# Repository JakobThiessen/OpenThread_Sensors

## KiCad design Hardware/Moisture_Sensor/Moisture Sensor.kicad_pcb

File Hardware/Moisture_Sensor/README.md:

# Moisture Sensor (OpenThread)  

> Kapazitiver Bodenfeuchtesensor mit ESP32-H2 und Matter over Thread  
> **Version 1.0 — April 2026**

## Fehler

Fehler im Schlatplan!!!
R7, Q1 und Q2 nicht bestücken.
Verbindung von Q1/pin1 zu Q2/Pin2 wie
eingezeichnet herstellen und mit GPIO
ein und ausschalten.

## Übersicht

Batteriebetriebener kapazitiver Bodenfeuchtesensor für den Einsatz im Smart Home. Die Kommunikation erfolgt drahtlos über **Matter over Thread** mittels eines **ESP32-H2 Supermini** Moduls.

Das Sensordesign misst die Bodenfeuchte kapazitiv über eine interdigitale Elektrodenstruktur auf der PCB-Sonde und nutzt einen **NE555** Timer zur Frequenzerzeugung. Die gemessene Frequenz wird vom ESP32-H2 ausgewertet und über das Thread-Netzwerk übermittelt.

## PCB

| Oberseite | Unterseite |
|-----------|------------|
|  |  |

### Abmessungen

| Parameter | Wert |
|-----------|------|
| Gesamtlänge (inkl. Sonde) | ca. 90 mm |
| Breite Elektronikteil | ca. 28,4 mm |
| Breite Sonde | ca. 14,2 mm |

## Hauptkomponenten

| Bauteil | Beschreibung |
|---------|-------------|
| **ESP32-H2 Supermini** | Mikrocontroller mit IEEE 802.15.4 (Thread) |
| **NE555D** | Timer-IC für kapazitive Frequenzmessung |
| **BSS84** | P-Kanal MOSFET (Stromversorgungsschaltung) |
| **BSS123** | N-Kanal MOSFET (Sensor-Enable-Schaltung) |
| **BAS19** | Schaltdiode |
| **3,7 V LiPo** | Lithium-Polymer-Akku (auf der Rückseite montiert) |

## Signale

| Signal | Funktion |
|--------|----------|
| `SensorEN` | Aktiviert die Sensorschaltung (Stromsparen) |
| `SensorOut` | Frequenzausgang des NE555 → ESP32-H2 |
| `Ubat_adc` | Batteriespannungsmessung über ADC |
| `IO4`, `IO5` | Weitere GPIOs des ESP32-H2 |

## Funktionsprinzip

1. Der ESP32-H2 aktiviert die Sensorschaltung über `SensorEN` (MOSFET-Schaltstufe: Q1 BSS123 → Q2 BSS84).
2. Der NE555 erzeugt ein Rechtecksignal, dessen Frequenz von der Kapazität der Sonde abhängt.
3. Die Sonde nutzt interdigitale Kupferflächen — eine höhere Bodenfeuchte erhöht die Kapazität und senkt die Frequenz.
4. Der ESP32-H2 misst die Frequenz am `SensorOut`-Pin und berechnet den Feuchtigkeitswert.
5. Nach der Messung wird die Sensorschaltung abgeschaltet, um Strom zu sparen.
6. Die Batteriespannung wird über `Ubat_adc` überwacht (Spannungsteiler R1/R6: 2MΩ/4,7MΩ → ca. 0,55 µA Ruhestrom).
7. Die Messwerte werden per **Matter over Thread** an den Thread Border Router gesendet.

## Schaltungsanalyse — NE555 Astable

### Timing-Beschaltung

Der NE555 ist als **Astable-Multivibrator** konfiguriert:

| Parameter | Bauteil | Wert |
|-----------|---------|------|
| Ra (VCC → Discharge) | R2 | 330 kΩ |
| Rb (Discharge → Threshold/Trigger) | R3 | 1,6 kΩ |
| C (Timing-Kondensator) | C3 | 470 pF |
| C_probe (Sonden-Kapazität) | PCB-Elektroden | variabel |
| CV-Bypass (Pin 5) | C6 | 10 nF |
| Abblock-Kondensator | C4 | 100 nF |

### Frequenzformel (NE555 Astable)

$$f = \frac{1{,}44}{(R_A + 2 \cdot R_B) \cdot C_{total}}$$

Mit $R_A = 330\,\text{k}\Omega$, $R_B = 1{,}6\,\text{k}\Omega$:

$$R_A + 2 \cdot R_B = 333{,}2\,\text{k}\Omega$$

Die Gesamtkapazität setzt sich zusammen aus dem Festkondensator C3 und der variablen Sondenkapazität:

$$C_{total} = C_3 + C_{probe} = 470\,\text{pF} + C_{probe}$$

### Berechnete Frequenzen

| Zustand | C_probe (geschätzt) | C_total | Frequenz |
|---------|---------------------|---------|----------|
| Nur C3 (kein Boden) | 0 pF | 470 pF | **9,19 kHz** |
| Luft / trockene Sonde | ~10 pF | 480 pF | **9,00 kHz** |
| Trockener Boden | ~50 pF | 520 pF | **8,31 kHz** |
| Mäßig feucht | ~150 pF | 620 pF | **6,97 kHz** |
| Nasser Boden | ~300 pF | 770 pF | **5,61 kHz** |
| Gesättigt / Wasser | ~500 pF | 970 pF | **4,46 kHz** |

**Erwarteter Frequenzbereich: ca. 4,5 kHz – 9,2 kHz**

### Duty Cycle

$$D = \frac{R_A + R_B}{R_A + 2 \cdot R_B} = \frac{331{,}6\,\text{k}}{333{,}2\,\text{k}} \approx 99{,}5\,\%$$

Das Signal ist stark asymmetrisch (sehr kurze Low-Pulse). Der ESP32-H2 sollte die **Periodendauer** oder **Frequenz** messen (z. B. per Timer-Capture), nicht das Tastverhältnis.

### Bewertung (KI) — Kann das Design funktionieren?

**Grundsätzlich: Ja**, mit folgenden Anmerkungen:

| Aspekt | Bewertung |
|--------|-----------|
| Frequenzbereich 4,5–9,2 kHz | Sehr gut messbar mit ESP32-H2 Timer/Counter |
| Auflösung | Bei 12-bit Timer-Capture ausreichende Auflösung über den gesamten Bereich |
| Power-Gating (BSS84/BSS123) | Sinnvolles Design für Batteriebetrieb |
| Batterie-Monitoring (2M/4,7M Teiler) | Sehr stromsparend (~0,55 µA), gutes Design |
| Interdigitale PCB-Sonde | Bewährtes Prinzip für kapazitive Feuchtemessung |

**Wichtiger Hinweis — Versorgungsspannung:**

> ⚠️ Der klassische **NE555** (bipolar) ist für **min. 4,5 V** spezifiziert. Bei **3,3 V** Betriebsspannung kann er unzuverlässig arbeiten oder gar nicht anlaufen. Es wird empfohlen, eine **CMOS-555-Variante** zu verwenden (z. B. **LMC555**, **TLC555**, **ICM7555**), die ab **1,5 V** arbeitet und zudem weniger Strom verbraucht. Der Footprint (SOIC-8) ist kompatibel.

### Tipps zur Kalibrierung

- Den Sensor in **trockener Luft** und in **Wasser** messen → Frequenz-Endwerte bestimmen.
- Einen linearen oder polynomialen Zusammenhang zwischen Frequenz und Feuchte kalibrieren.
- Die Sondenkapazität hängt stark von Bodenart und Temperatur ab — eine Vor-Ort-Kalibrierung ist sinnvoll.

## Projektdateien

| Datei | Inhalt |
|-------|--------|
| `Moisture Sensor.kicad_sch` | Schaltplan |
| `Moisture Sensor.kicad_pcb` | PCB-Layout |
| `Moisture Sensor.kicad_pro` | KiCad-Projektdatei |
| `Moisture Sensor.step` | 3D-Modell der Platine |
| `Moisture Sensor.pdf` | Schaltplan als PDF |
| `lib/` | Bauteilbibliotheken (Symbole, Footprints, 3D-Modelle) |

## Voraussetzungen

- [KiCad 9.0](https://www.kicad.org/) oder neuer
- Thread Border Router (z. B. Apple HomePod, Google Nest Hub) für die Matter-Integration

## Lizenz

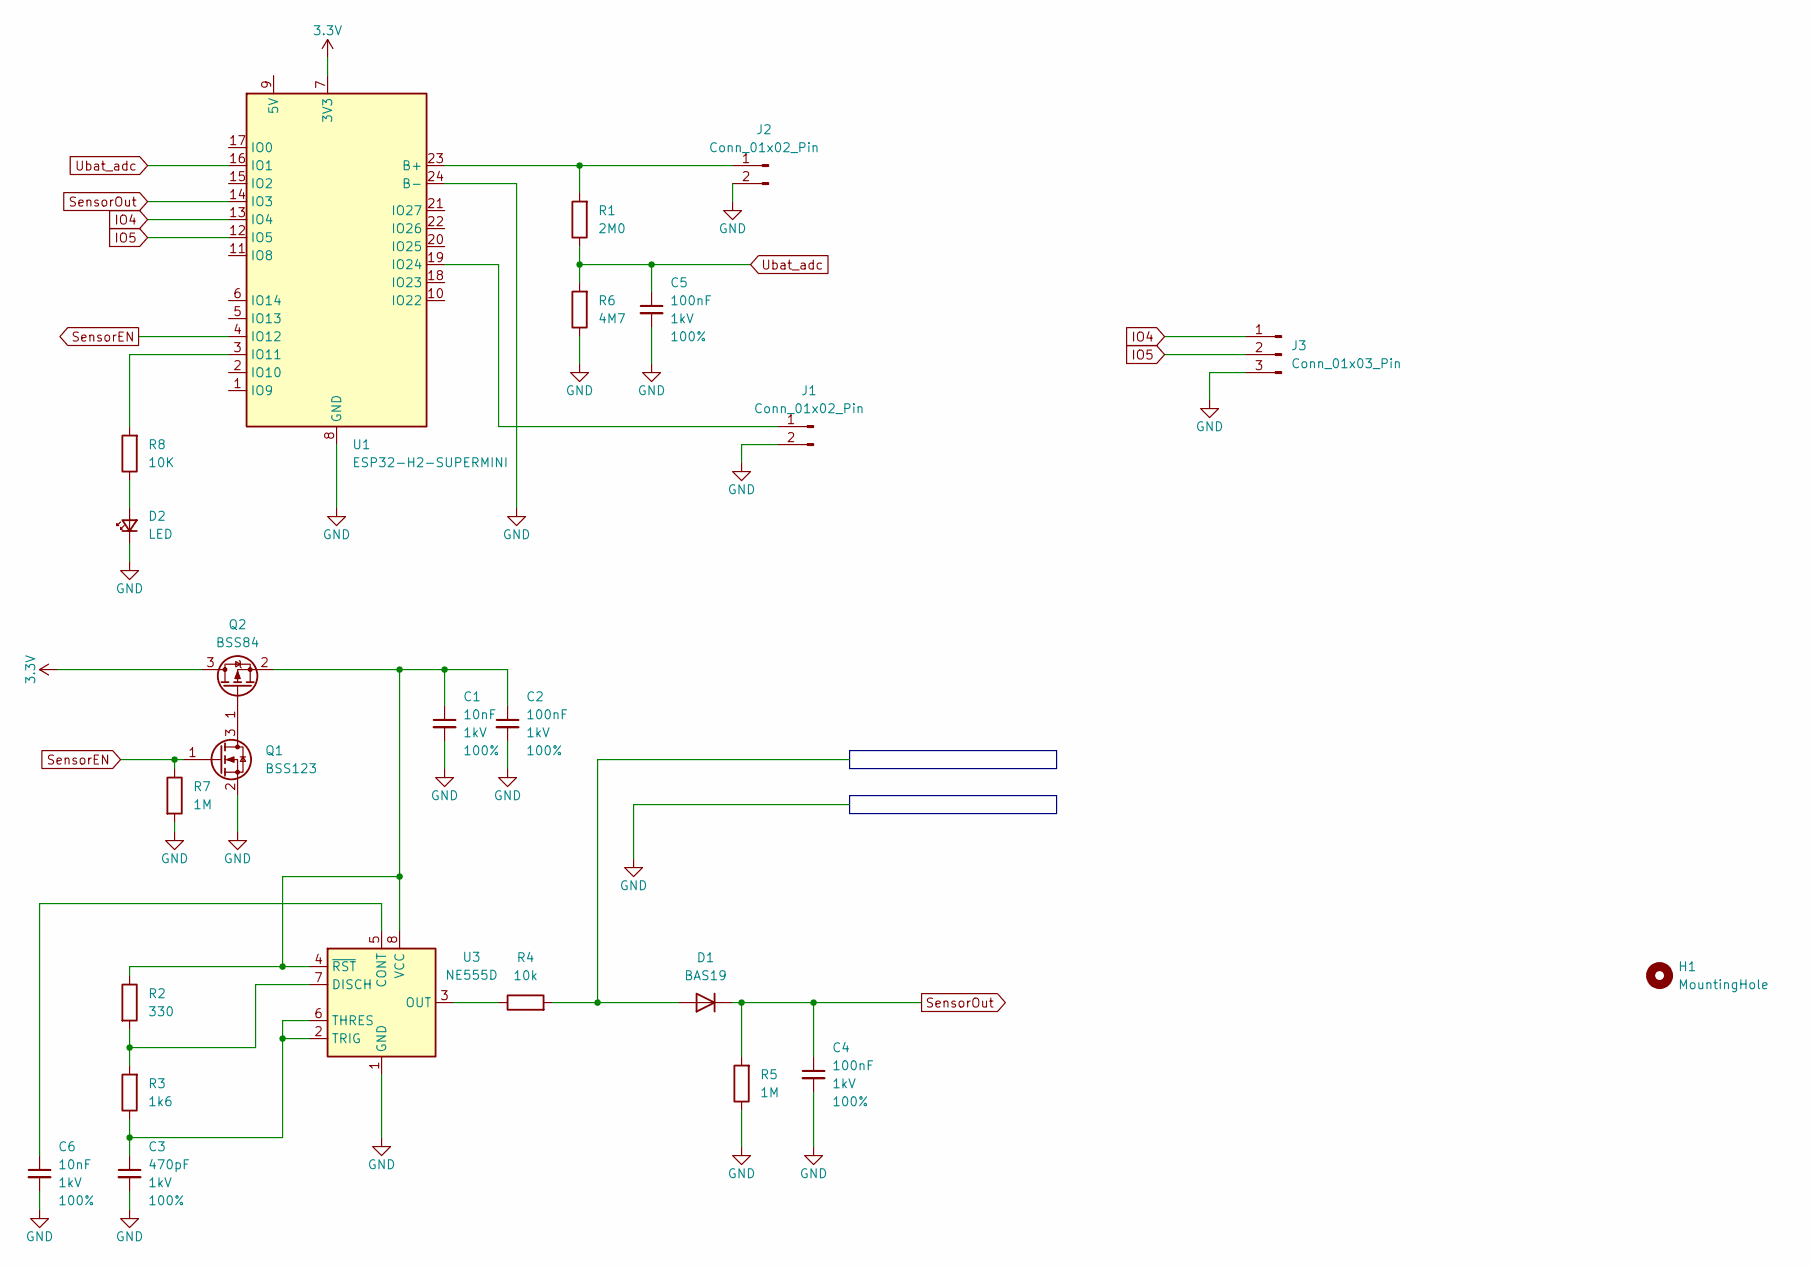
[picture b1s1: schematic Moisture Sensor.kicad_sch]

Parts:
C1, C6: 10nF; C_0603_1608Metric; Voltage 1kV; Tolerance 100%
C2, C4, C5: 100nF; C_0603_1608Metric; Voltage 1kV; Tolerance 100%
C3: 470pF; C_0603_1608Metric; Voltage 1kV; Tolerance 100%
D1: BAS19; SOT-23
D2: LED; LED_0603_1608Metric
H1: MountingHole; MountingHole_2.5mm
J1, J2: Conn_01x02_Pin; PinHeader_1x02_P2.54mm_Vertical
J3: Conn_01x03_Pin; PinHeader_1x03_P2.54mm_Vertical
Q1: BSS123; SOT-23
Q2: BSS84; SOT-23
R1: 2M0; R_0603_1608Metric
R2: 330; R_0603_1608Metric
R3: 1k6; R_0603_1608Metric
R4: 10k; R_0603_1608Metric
R5, R7: 1M; R_0603_1608Metric
R6: 4M7; R_0603_1608Metric
R8: 10K; R_0603_1608Metric
U1: ESP32-H2-SUPERMINI; ESP32H2-Supermini
U3: NE555D; SOIC-8_3.9x4.9mm_P1.27mm

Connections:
3.3V: Q2.3 (D), U1.7 (3V3)
GND: C1.2, C2.2, C3.2, C4.2, C5.2, C6.2, D2.1 (K), J1.2, J2.2, J3.3, Q1.2 (S), R5.1, R6.1, R7.2, U1.8 (GND), U1.24 (B-), U3.1 (GND)
IO4: J3.1, U1.13 (IO4)
IO5: J3.2, U1.12 (IO5)
unnamed: D1.1 (A), R4.2
unnamed: D2.2 (A), R8.1
unnamed: J1.1, U1.19 (IO24)
unnamed: J2.1, R1.2, U1.23 (B+)
unnamed: Q1.3 (D), Q2.1 (G)
unnamed: C1.1, C2.1, Q2.2 (S), R2.1, U3.4 (~RST), U3.8 (VCC)
unnamed: R8.2, U1.3 (IO11)
unnamed: C6.1, U3.5 (CONT)
unnamed: R2.2, R3.2, U3.7 (DISCH)
unnamed: R4.1, U3.3 (OUT)
unnamed: C3.1, R3.1, U3.2 (TRIG), U3.6 (THRES)
SensorEN: Q1.1 (G), R7.1, U1.4 (IO12)
SensorOut: C4.1, D1.3 (K), R5.2, U1.14 (IO3)
Ubat_adc: C5.1, R1.1, R6.2, U1.16 (IO1)

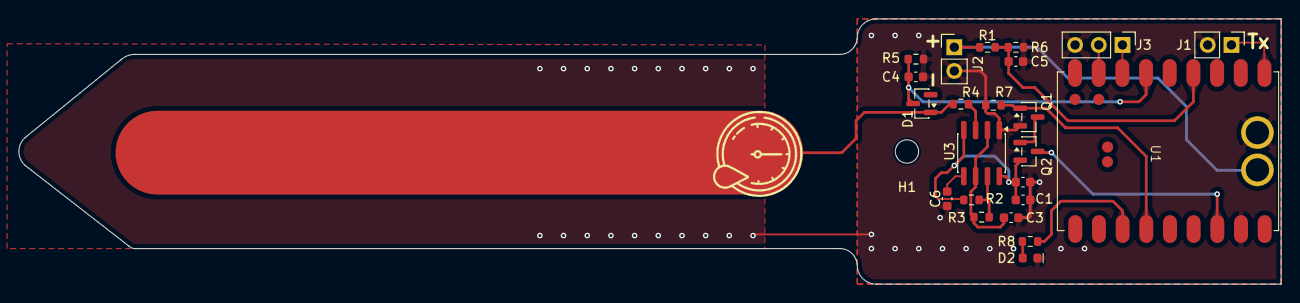
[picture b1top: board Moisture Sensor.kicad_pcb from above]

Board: 2 copper layers, 135.4 x 28.4 mm, 24 parts (0 on the bottom side), 18 nets.

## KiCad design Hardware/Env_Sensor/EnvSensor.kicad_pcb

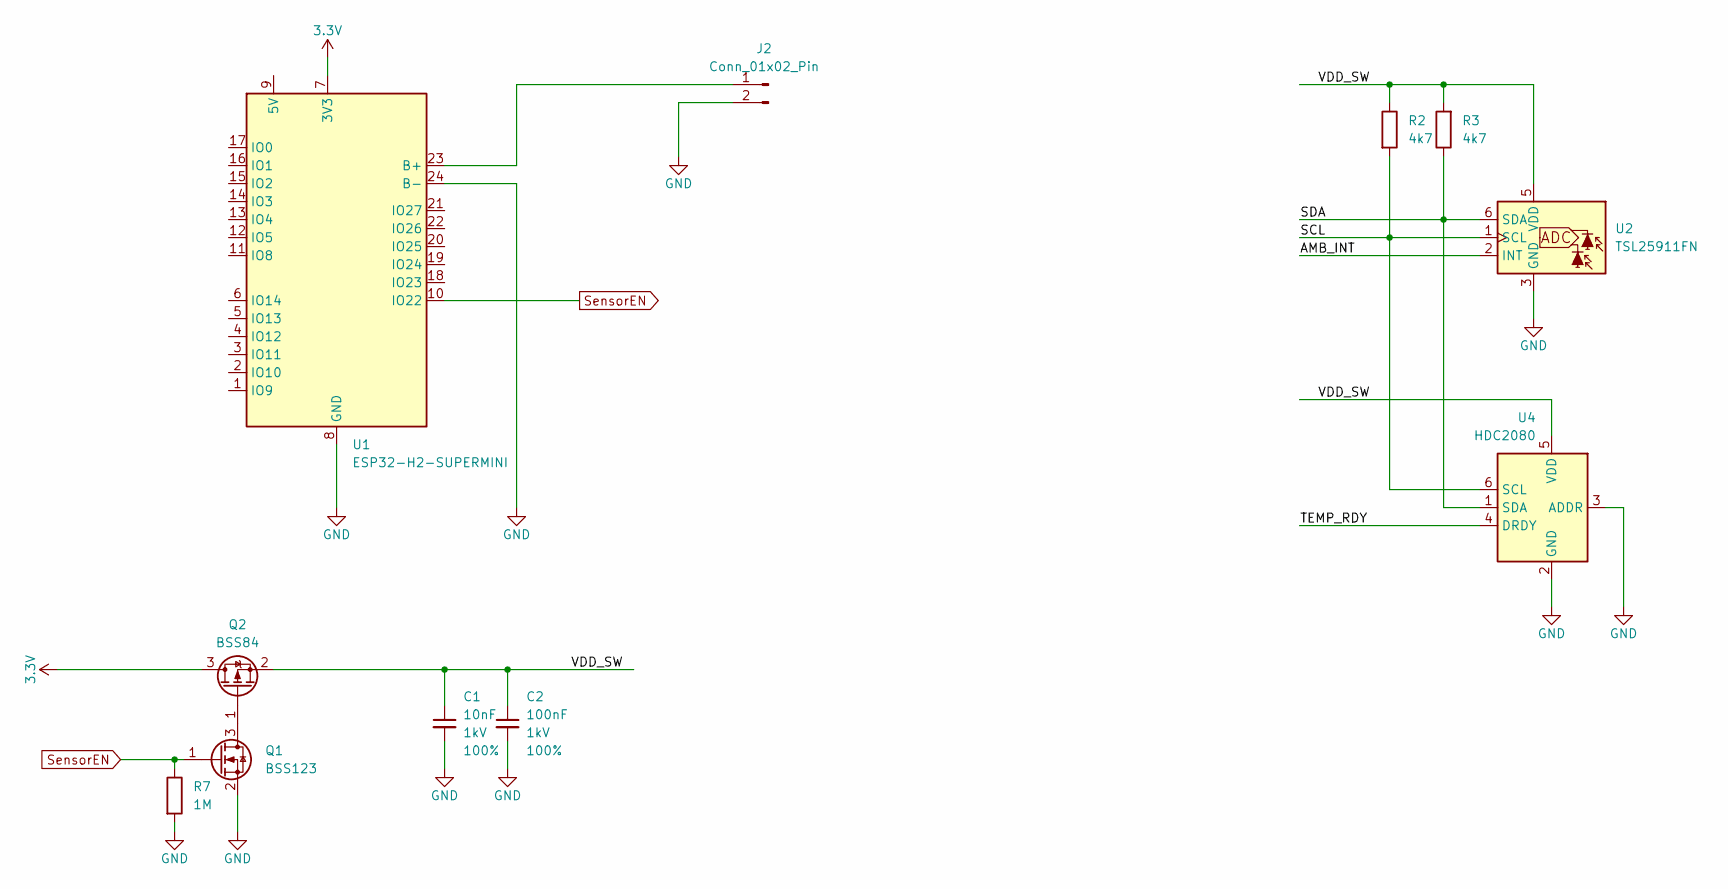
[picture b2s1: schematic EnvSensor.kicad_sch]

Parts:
C1: 10nF; C_0603_1608Metric; Voltage 1kV; Tolerance 100%
C2: 100nF; C_0603_1608Metric; Voltage 1kV; Tolerance 100%
J2: Conn_01x02_Pin; PinHeader_1x02_P2.54mm_Vertical
Q1: BSS123; SOT-23
Q2: BSS84; SOT-23
R2, R3: 4k7; R_0603_1608Metric
R7: 1M; R_0603_1608Metric
U1: ESP32-H2-SUPERMINI; ESP32H2-Supermini
U2: TSL25911FN; AMS_TSL25911FN
U4: HDC2080; Texas_S-PWSON-N6-HDC2080

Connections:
3.3V: Q2.3 (D), U1.7 (3V3)
/AMB_INT: U2.2 (INT)
/SCL: R2.2, U2.1 (SCL), U4.6 (SCL)
/SDA: R3.1, U2.6 (SDA), U4.1 (SDA)
/TEMP_RDY: U4.4 (DRDY)
/VDD_SW: C1.1, C2.1, Q2.2 (S), R2.1, R3.2, U2.5 (VDD), U4.5 (VDD)
GND: C1.2, C2.2, J2.2, Q1.2 (S), R7.2, U1.8 (GND), U1.24 (B-), U2.3 (GND), U4.2 (GND), U4.3 (ADDR)
unnamed: J2.1, U1.23 (B+)
unnamed: Q1.3 (D), Q2.1 (G)
SensorEN: Q1.1 (G), R7.1, U1.10 (IO22)

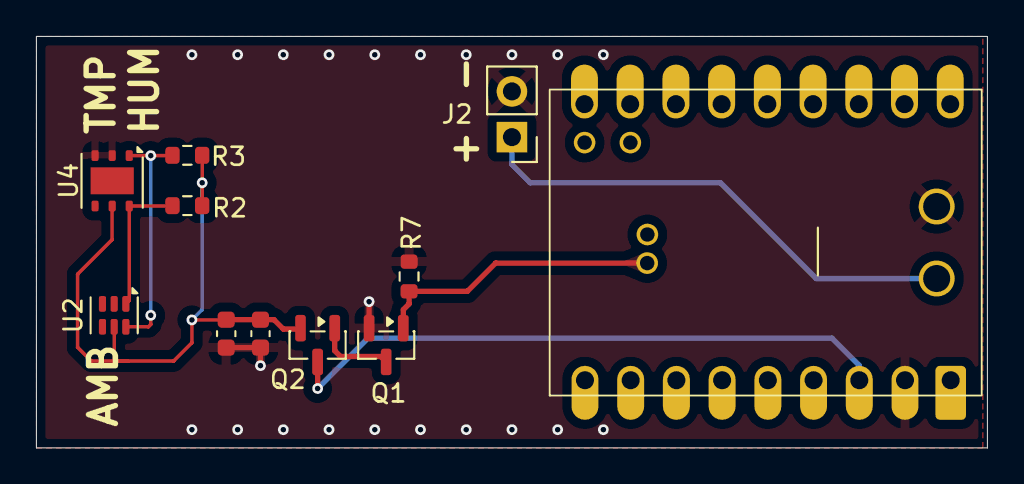
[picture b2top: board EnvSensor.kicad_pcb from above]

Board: 2 copper layers, 52.8 x 22.9 mm, 11 parts (0 on the bottom side), 8 nets.

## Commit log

2026-03-04 initial
2026-04-19 rename Hygrometer_Sensor to Moisture_Sensor
2026-04-19 layout angepasst. dokumentation hinzugefügt
2026-04-19 README.md angepasst
2026-04-19 aktuelle pdf's erzeugt
2026-04-19 gerberdatei erstellt
2026-05-08 R2 auf 330 geändert und R5 auf 1Meg
2026-05-08 pdf neu erzeugt
2026-05-08 Fehler im Schlatplan!!! R7, Q1 und Q2 nicht bestücken. Verbindung von Q1/pin1 zu Q2/Pin2 wie eingezeichnet herstellen und mit GPIO ein und ausschalten.
